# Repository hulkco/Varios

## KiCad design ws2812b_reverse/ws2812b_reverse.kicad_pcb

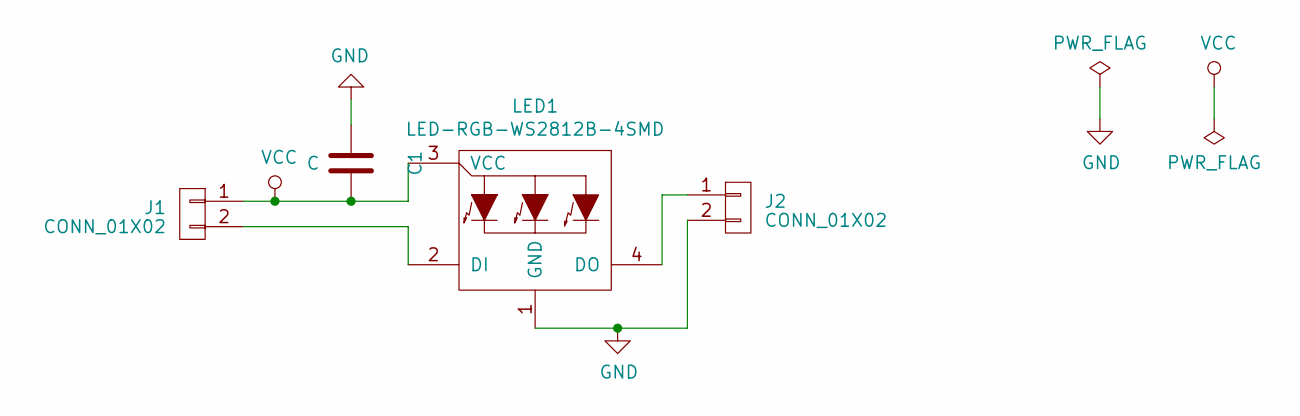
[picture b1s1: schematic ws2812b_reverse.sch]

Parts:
C1: C; C_1206_3216Metric_Pad1.39x1.80mm_HandSolder
J1, J2: CONN_01X02; Pin_half-02x02_P2.54mm
LED1: LED-RGB-WS2812B-4SMD; LED-RGB-5050-SMD

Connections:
GND: C1.2, J2.2, LED1.1 (GND)
unnamed: J1.2, LED1.2 (DI)
unnamed: J2.1, LED1.4 (DO)
VCC: C1.1, J1.1, LED1.3 (VCC)

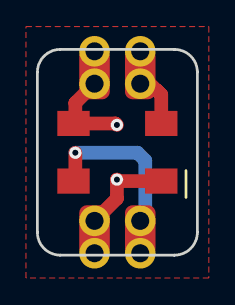
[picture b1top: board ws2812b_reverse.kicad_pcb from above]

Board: 2 copper layers, 8.9 x 11.4 mm, 4 parts (1 on the bottom side), 4 nets.
